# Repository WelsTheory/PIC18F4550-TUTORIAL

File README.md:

# PIC18F4550-TUTORIAL
HOLA! Yo soy Wels.
En este repositorio encontrarás todos los archivos, documentos y ejemplos del tutorial del microcontrolador Pic18F4550
Los vídeos los puedes encontrar en mi canal: https://www.youtube.com/wels_theory
Cualquier duda, sugerencia o comentario me lo puedes hacer a:
FB: https://www.facebook.com/welstheory
Twitter:https://twitter.com/soywels

***************************************************Creado el 31/12/2017*****************************************************

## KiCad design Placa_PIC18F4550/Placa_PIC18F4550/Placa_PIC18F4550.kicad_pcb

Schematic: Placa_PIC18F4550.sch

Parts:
C1: 47uF; CP_Radial_D6.3mm_P2.50mm
C2, C3: 15pF; C_Disc_D3.8mm_W2.6mm_P2.50mm
C4: 100nF; C_Disc_D3.8mm_W2.6mm_P2.50mm
C5: 220uF; CP_Radial_D10.0mm_P2.50mm
D1, D4: LED; LED_D5.0mm
D2, D3: 1N4148; D_DO-35_SOD27_P7.62mm_Horizontal
J1: PORTD; PinSocket_1x08_P2.54mm_Vertical
J2: PORTA; PinSocket_1x07_P2.54mm_Vertical
J3: PORTE; PinSocket_1x03_P2.54mm_Vertical
J4: PORTB; PinSocket_1x08_P2.54mm_Vertical
J5: PORTC; PinSocket_1x07_P2.54mm_Vertical
J6: GND; PinSocket_1x03_P2.54mm_Vertical
J7: Vol; PinSocket_1x03_P2.54mm_Vertical
J8: Volt; PinHeader_1x03_P2.54mm_Vertical
J9: Barrel_Jack_Switch; Jack_Horizontal
J10: USB_B; USB_B_OST_USB-B1HSxx_Horizontal
J11: PICKIT; PinHeader_1x06_P2.54mm_Vertical
J12: Conn_01x02_Male; PinHeader_1x02_P2.54mm_Vertical
Q1: 2N3906; TO-92L_Inline_Wide
R1, R3, R6: 10k; R_Axial_DIN0207_L6.3mm_D2.5mm_P7.62mm_Horizontal
R2: 330; R_Axial_DIN0207_L6.3mm_D2.5mm_P7.62mm_Horizontal
R4, R5: 5.6K; R_Axial_DIN0207_L6.3mm_D2.5mm_P7.62mm_Horizontal
R7: 470; R_Axial_DIN0207_L6.3mm_D2.5mm_P7.62mm_Horizontal
SW1: SW_Push; SW_PUSH_6mm
U1: PIC18F4550-IP; DIP-40_W15.24mm
U2: L7805; TO-220-3_Vertical
Y1: 20MHz; Crystal_HC50_Vertical

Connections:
/MCLR: J11.1, R1.2, SW1.2, U1.1 (Vpp/~MCLR~/RE3)
/OS1: C2.2, U1.13 (OSC1/CLKI), Y1.1
/OS2: C3.2, J2.7, U1.14 (RA6/OSC2/CLKO), Y1.2
/RA0: J2.1, U1.2 (RA0/AN0)
/RA1: J2.2, U1.3 (RA1/AN1)
/RA2: J2.3, U1.4 (RA2/AN2/Vref-/CVref)
/RA3: J2.4, U1.5 (RA3/AN3/Vref+)
/RA4: J2.5, U1.6 (RA4/T0CKI/C1OUT/RCV)
/RA5: J2.6, U1.7 (RA5/AN4/~SS~/HLVDIN/C2OUT)
/RB0: J4.1, U1.33 (RB0/AN12/INT0/FLT0/SDI/SDA)
/RB1: J4.2, U1.34 (RB1/AN10/INT1/SCK/SCL)
/RB2: J4.3, U1.35 (RB2/AN8/INT2/VMO)
/RB3: J4.4, U1.36 (RB3/AN9/CCP2/VPO)
/RB4: J4.5, U1.37 (RB4/AN11/KBI0/CSSPP)
/RB5: J4.6, J11.6, U1.38 (RB5/KBI1/PGM)
/RB6: J4.7, J11.5, U1.39 (RB6/KBI2/PGC)
/RB7: J4.8, J11.4, U1.40 (RB7/KBI3/PGD)
/RC0: J5.1, U1.15 (T1OSO/T13CKI/RC0)
/RC1: J5.2, U1.16 (~UOE~/CCP2/T1OSI/RC1)
/RC2: J5.3, U1.17 (P1A/CCP1/RC2)
/RC4: J5.4, J10.2, U1.23 (VM/D-/RC4)
/RC5: J5.5, J10.3, U1.24 (VP/D+/RC5)
/RC6: J5.6, U1.25 (TX/CK/RC6)
/RC7: J5.7, U1.26 (SDO/RX/DT/RC7)
/RD0: J1.1, J12.2, U1.19 (SPP0/RD0)
/RD1: J1.2, U1.20 (SPP1/RD1)
/RD2: J1.3, U1.21 (SPP2/RD2)
/RD3: J1.4, U1.22 (SPP3/RD3)
/RD4: J1.5, U1.27 (SPP4/RD4)
/RD5: J1.6, U1.28 (P1B/SPP5/RD5)
/RD6: J1.7, U1.29 (P1C/SPP6/RD6)
/RD7: J1.8, U1.30 (P1D/SPP7/RD7)
/RE0: J3.1, U1.8 (CK1SPP/AN5/RE0)
/RE1: J3.2, U1.9 (CK2SPP/AN6/RE1)
/RE2: J3.3, U1.10 (OESPP/AN7/RE2)
/V+: J8.1, J11.2
/VUSB: J10.1, Q1.1, R3.1, R6.2
/Vc: C5.1, D3.1, J8.3, Q1.3, R7.1
GND: C1.2, C2.1, C3.1, C4.2, C5.2, D1.1, D2.1, D4.1, J6.1, J6.2, J6.3, J9.2, J9.3, J10.4, J10.5, J11.3, R3.2, R4.1, R6.1, SW1.1, U1.12 (VSS), U1.31 (VSS)
unnamed: C1.1, U1.18 (VUSB)
unnamed: C4.1, D3.2, R4.2, R5.2, U2.3
unnamed: D1.2, R2.2
unnamed: D2.2, U2.2
unnamed: D4.2, R7.2
unnamed: J9.1, U2.1
unnamed: J12.1, R2.1
unnamed: Q1.2, R5.1
VCC: J7.1, J7.2, J7.3, J8.2, R1.1, U1.11 (VDD), U1.32 (VDD)

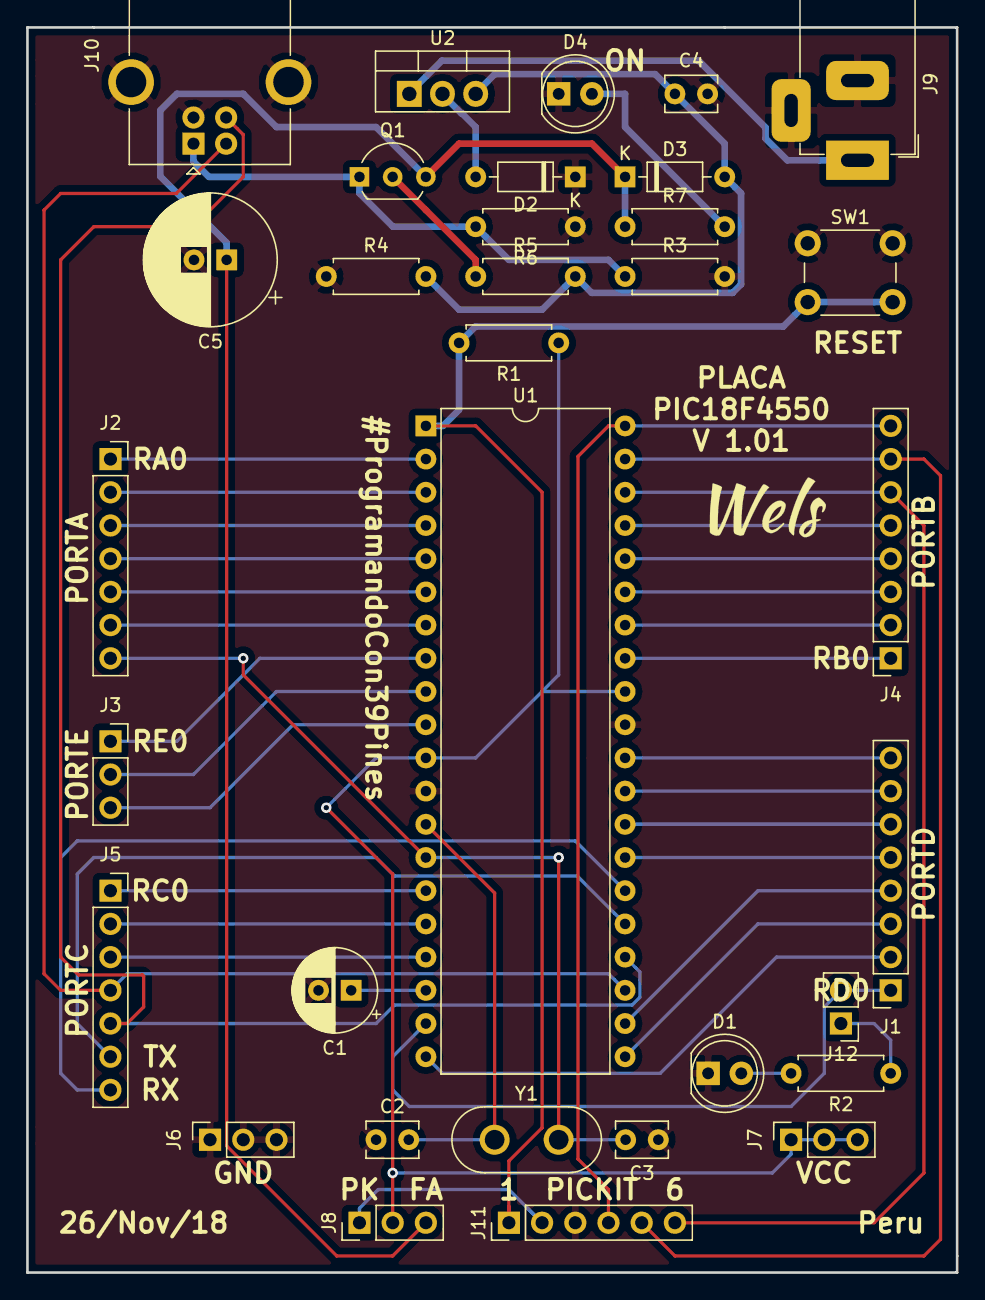
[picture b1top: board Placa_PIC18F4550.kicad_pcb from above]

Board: 2 copper layers, 71.1 x 95.2 mm, 33 parts (0 on the bottom side), 48 nets.

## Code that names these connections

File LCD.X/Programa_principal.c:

/*

 * Tutorial 4 PIC18F4550 - LCD

 * Descripción: Como mostrar caracteres en el LCD usando el PIC18F4550!  

 * Autor:           Wels (@soywels) 
 
 * Copyright: 		Wels Theory 2018

 * Fecha			16 de Febrero del 2018
  
 * Facebook:        https://www.facebook.com/welstheory
 
 * Youtube:         https://www.youtube.com/wels_theory
 
 * Instagram:       https://www.instagram.com/wels_theory/  

 */


#include <xc.h>
#include "Configuracion.h"
#include "LCD_libreria.h"

//Wels
const char wels[]={     0b00000111,
                        0b00001110,
                        0b00000101,
                        0b00001110,
                        0b00010100,
                        0b00001010,
                        0b00010001,
                        0b00000000,0
};
const char wels1[]={    0b00000111,
                        0b00001110,
                        0b00000100,
                        0b00001111,
                        0b00010100,
                        0b00001010,
                        0b00010001,
                        0b00000000,0};
//Pokeball
const char pokeball[]={ 0b00000000,
                        0b00000000,
                        0b00001110,
                        0b00010001,
                        0b00011011,
                        0b00010001,
                        0b00001110,
                        0b00000000,0};
//Pikachu
const char pikachu[]={  0b00010001,
                        0b00001110,
                        0b00001110,
                        0b00000100,
                        0b00011111,
                        0b00001110,
                        0b00011011,
                        0b00000000,0};
//Squirtle
const char squirtle[]={ 0b00000000,
                        0b00001110,
                        0b00001110,
                        0b00000100,
                        0b00011111,
                        0b00001110,
                        0b00010001,
                        0b00000000,0};
//Bulbasaur
const char bulbasaur[]={0b00000000,
                        0b00000100,
                        0b00001110,
                        0b00011111,
                        0b00001110,
                        0b00001110,
                        0b00001010,
                        0b00000000,0};
//Charmander
const char charmander[]={0b00001110,
                         0b00001110,
                         0b00000100,
                         0b00011111,
                         0b00001110,
                         0b00001111,
                         0b00001010,
                         0b00000000,0};

void LCD_Init(void){
    OpenXLCD(FOUR_BIT & LINES_5X7 );
    while(BusyXLCD()); // LCD esta ocupado
    WriteCmdXLCD(0x06); //Mover el cursor a la derecha
    WriteCmdXLCD(0x0C); //Desactivar el cursor
}

void InitPort(void){
    ADCON1bits.PCFG = 0xFF; //Pines en digital
    TRISBbits.RB0 = 1;
    TRISBbits.RB7 = 1;
    TRISBbits.RB5 = 1;
    TRISBbits.RB4 = 1;
    TRISBbits.RB2 = 1;
    INTCON2bits.RBPU = 0;  //Resistencias Pull-Up 
}


void main(void) {
    LCD_Init();
    InitPort();
    LCD_gotoXY(0,0);
    putrsXLCD("**POKEMON GO!***");
    __delay_ms(100);
    LCD_gotoXY(1,0);
    putrsXLCD("Presiona Start!!");
    __delay_ms(100);
    if(PORTBbits.RB0 == 0){
        WriteCmdXLCD(BORRAR_LCD);
        LCD_WriteChr_CGRAM(wels,0);
        LCD_WriteChr_CGRAM(wels1,1);
        LCD_WriteChr_CGRAM(pokeball,3);
        LCD_WriteChr_CGRAM(pikachu,4);
        LCD_WriteChr_CGRAM(charmander,5);
        LCD_WriteChr_CGRAM(squirtle,6);
        LCD_WriteChr_CGRAM(bulbasaur,7);
        __delay_ms(500);
        while(1){
            LCD_gotoXY(0,0);
            putrsXLCD("Wels Ketchup");
            __delay_ms(500);
            LCD_gotoXY(1,0);
            putcXLCD(0);
            __delay_ms(200);
            if(PORTBbits.RB7 == 0){
                WriteCmdXLCD(BORRAR_LCD);
                __delay_ms(5);
                LCD_gotoXY(1,0);
                putcXLCD(1);
                __delay_ms(100);
                LCD_gotoXY(1,3);
                putcXLCD(3);
                __delay_ms(100);
                LCD_gotoXY(1,5);
                putcXLCD(4);
                __delay_ms(100);
                LCD_gotoXY(0,0);
                putrsXLCD("ES PIKACHU!!");
                __delay_ms(1500);
                WriteCmdXLCD(BORRAR_LCD);
                __delay_ms(5);
            }
            if(PORTBbits.RB5 == 0){
                WriteCmdXLCD(BORRAR_LCD);
                __delay_ms(5);
                LCD_gotoXY(1,0);
                putcXLCD(1);
                __delay_ms(100);
                LCD_gotoXY(1,3);
                putcXLCD(3);
                __delay_ms(100);
                LCD_gotoXY(1,5);
                putcXLCD(5);
                __delay_ms(100);
                LCD_gotoXY(0,0);
                putrsXLCD("ES CHARMANDER!!");
                __delay_ms(1500);
                WriteCmdXLCD(BORRAR_LCD);
                __delay_ms(5);
            }
            if(PORTBbits.RB4 == 0){
                WriteCmdXLCD(BORRAR_LCD);
                __delay_ms(5);
                LCD_gotoXY(1,0);
                putcXLCD(1);
                __delay_ms(100);
                LCD_gotoXY(1,3);
                putcXLCD(3);
                __delay_ms(100);
                LCD_gotoXY(1,5);
                putcXLCD(6);
                __delay_ms(100);
                LCD_gotoXY(0,0);
                putrsXLCD("ES SQUIRTLE!!");
                __delay_ms(1500);
                WriteCmdXLCD(BORRAR_LCD);
                __delay_ms(5);
            }
            if(PORTBbits.RB2 == 0){
                WriteCmdXLCD(BORRAR_LCD);
                __delay_ms(5);
                LCD_gotoXY(1,0);
                putcXLCD(1);
                __delay_ms(100);
                LCD_gotoXY(1,3);
                putcXLCD(3);
                __delay_ms(100);
                LCD_gotoXY(1,5);
                putcXLCD(7);
                __delay_ms(100);
                LCD_gotoXY(0,0);
                putrsXLCD("ES BULBASAUR!!");
                __delay_ms(1500);
                WriteCmdXLCD(BORRAR_LCD);
                __delay_ms(5);
            }
        }
    }
    
}

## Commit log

2018-01-01 Descripción del Tutorial PIC18F4550
2018-01-01 Circuito-Fundamentos Básicos PIC18F4550
2018-01-06 Tutorial 1 - Pic18f4550
2018-01-19 Tutorial 2 - Pulsadores!
2018-02-01 Pequeñas modificaciones
2018-02-18 Tutorial LCD PIC18f4550
2018-02-19 Generar caracter en Excel!
2018-03-09 Tutorial TIMER0 PIC18F4550
2018-03-09 TIMER0 PIC18F4550
2018-05-05 Tutorial PWM - PIC18F4550
2018-05-15 COMO VARIAR EL PWM USANDO FOR Y PULSADORES
2018-05-23 TUTORIAL ADC
2018-07-12 Proyecto ADC
2018-07-20 USART PIC18F4550
2018-08-03 Bluetooth pic18f4550
2018-08-16 MOTOR USART
2018-08-23 Proteus de Display 7 Seg
2018-08-23 Terminal
2018-10-09 Interrupción externa
2018-11-16 Programa e interfaz del USB
2018-12-12 Placa PCB PIC18f4550
2018-12-25 Modificación de archivos Gerber!
2019-02-11 Actualicación de documentos
2019-03-01 Configuracion LCD!
2019-03-06 MEMORIA EEPROM
2019-03-14 EEPROM Variables
2019-04-06 Servomotor
2019-04-12 Modo Sleep
2019-05-31 Programa SPI
2020-07-10 USART Cadena
2020-08-27 Tutorial I2C
2020-09-15 I2C DS1307
